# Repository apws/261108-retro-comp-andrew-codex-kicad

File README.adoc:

= Andrew's Z80: Codex KiCad experiments
:title: {docname}
:toc:

*2026-11-10:* The link:schematics/03-schematic-7805/schematic-7805.kicad_pro[separate 7805 supply schematic] and link:docs/261110-0001-DONE-schematic-7805-and-readable-wiring.adoc[wired-drawing readability cleanup] are complete. The new link:firstz80/README.adoc[FirstZ80 comparison] preserves Andrew's exact historical placement in three checked outputs: Manhattan, an explicitly labelled octilinear hybrid, and FreeRouting with a recorded native clearance correction. See link:docs/261110-0004-DONE-FirstZ80-fixed-placement-routing.adoc[the results, source differences and limitations] or link:output/firstz80/comparison.png[the comparison overview]. This is a separate two-layer series from the earlier four-layer experiments below.

*2026-11-09:* A separate link:schematics/02-wired-a3/Z80_Simple_Computer.kicad_pro[wired single-A3 schematic] is now available, with link:output/pdf/Z80_Simple_Computer-wired-A3.pdf[PDF] and link:output/schematic-wired-a3/Z80_Simple_Computer.png[PNG] previews. It preserves all 301 pin assignments, passes ERC, and retains the original schematic and completed board variants unchanged. See link:docs/261109-1528-SCHEMATIC-wired-A3.adoc[the drawing handover].

Falken's subsequent presentation refinements are retained in this human-edited version. See link:docs/261109-1549-REVIEW-human-schematic-corrections.adoc[the human-corrections review], including two unintended wiring changes repaired, six label anchors reattached and compact reminders for later sessions. The current result again matches all 301 original pin assignments with zero ERC findings.

link:docs/261109-2306-REVIEW-Mark-schematic-readability.adoc[Mark's subsequent readability review] preserves his feedback verbatim, confirms the connected but ambiguous PPI reset-pin approach, and records text/pin clearance lessons for our own drawing style. Fresh ERC and all 301 pin assignments still pass; this review does not change the schematic or resume PCB routing.

== Start here, Andrew

This repository preserves three completed routing experiments on the same 160 x 100 mm, four-layer Z80 board placement. Open the FreeRouting project first for the most economical completed routing in this comparison, then compare the saved alternatives. The original GIF and Grok/AGY project are under `reference/`.

[cols="2,1,1,3",options="header"]
|===
|Experiment |Added signal vias |Signal copper |KiCad project
|1: adapted AGY Manhattan router |212 |5,413.942 mm |link:layouts/01-reused-agy-router/Z80_Simple_Computer.kicad_pro[Open variant 1]
|2: Codex octilinear router |129 |4,959.519 mm |link:layouts/02-codex-router/Z80_Simple_Computer.kicad_pro[Open variant 2]
|4: FreeRouting, local MCP |12 |4,856.931 mm |link:layouts/04-freerouting/Z80_Simple_Computer.kicad_pro[Open variant 4]
|===

All three completed boards passed fresh native ERC/DRC/connectivity/parity checks before the initial Git snapshot. Variant 3 is the prepared native interactive experiment and remains pending. These are design experiments; hardware and signal integrity have not been qualified. FreeRouting's separate CLI controls remained incomplete and are retained as evidence.

The repository includes the required symbol, footprint and STEP library subset. Clone it with Git to preserve the relative library symlinks. The projects were checked with KiCad 10.0.8. See link:docs/261108-2026-HANDOVER-GitHub-and-next-review.adoc[publication checks, reproduction instructions and next review] for the handover.

== Working notes

The Asciidoctor.js CSS/JavaScript rendering setup is by Falken (https://mixworx.net[mixworx.net]). The local JavaScript helper also contains the filename-to-print-title adaptation described below.

Name new AsciiDoc notes under `docs/` with a `YYMMDD-HHMM` prefix, followed by a descriptive title.

New notes also use `:title: {docname}` for the HTML browser/print title. For Asciidoctor.js Live Preview, select this project's `asciidoctorjs-crx-mixworx.js` as the custom JavaScript, loaded *after* rendering, then reload the note. It retains the shared heading/key formatting and sets the tab title from the source filename, so Chromium's Save as PDF can suggest the matching `.pdf` name. See link:docs/261108-1513-DOCS-PDF-filenames.adoc[setup and verification].

*Current result:* link:docs/261108-1641-DONE-FreeRouting-MCP-and-CLI.adoc[variant 4, official local FreeRouting MCP, is fully routed and verified], with 12 vias and 4,856.931 mm of signal copper. Final ERC, DRC, unconnected and parity counts are all zero. Open link:layouts/04-freerouting/Z80_Simple_Computer.kicad_pro[the FreeRouting KiCad project] or view link:output/routing/04-freerouting/signals.png[its routing] and link:output/routing/04-freerouting/3d-top.png[3D render]. Two CLI controls remained incomplete with six connections; they are recorded separately and were not promoted as finished results.

link:docs/261108-1601-DONE-Codex-router-comparison.adoc[Variant 2, the Codex octilinear router], is preserved at 129 vias and 4,959.519 mm of signal copper, on the same placement/circuit/rules. Open link:layouts/02-codex-router/Z80_Simple_Computer.kicad_pro[its KiCad project] or link:output/routing/02-codex-router/signals.png[routing preview].

link:docs/261108-1535-DONE-routing-and-comparison.adoc[Variant 1, the adapted AGY router], remains preserved and verified: 212 vias / 5,413.942 mm. Open link:layouts/01-reused-agy-router/Z80_Simple_Computer.kicad_pro[its KiCad project] or link:output/routing/01-reused-agy-router/signals.png[routing preview]. The historical Grok/AGY board remains available for context at 229 vias / 5,036.484 mm.

The link:docs/261108-1507-RECOVERY-current-state.adoc[earlier recovery note] records the previous stopping point and conversation gap. Its schematic/placement milestone was followed by the completed routing above.

Start with link:docs/261108-1419-PLAN.adoc[the experiment plan] and link:docs/261108-1422-PLAN-project-layouts.adoc[the agreed project organization].

`design/Z80_Simple_Computer.kicad_pro` is the authoritative circuit project. It now contains the Codex A3 schematic base, generated from an explicit pin specification and checked against the source GIF and inherited netlist. See link:docs/261108-1438-SCHEMATIC-base.adoc[the schematic handover] and `design/provenance.json`.

Open link:output/schematic/Z80_Simple_Computer.svg[the schematic preview] or link:output/schematic/Z80_Simple_Computer.png[the PNG rendering]. The native netlist and CSV BOM are in `output/schematic/`; ERC and connectivity reports are in `reports/schematic/`.

`layouts/` contains four ordinary KiCad project folders for the AGY-router reuse, Codex-router, interactive-KiCad, and FreeRouting experiments. Each has its own project settings and a synchronized schematic. Variants 1, 2 and 4 now contain completed routed Eurocards. link:docs/261108-1613-PENDING-native-interactive.adoc[Variant 3 is prepared and remains unrouted] for a later native GUI/control session; its worksheet and initial checks are saved. The completed historical board remains under `reference/grok-agy/`.

The link:docs/261108-1500-PLACEMENT-checkpoint.adoc[placement handover] includes a link:output/placement/3d-top.png[3D preview], verification and reproduction commands. `checkpoints/01-codex-placed-unrouted/` preserves the common routing input with file hashes. That untouched checkpoint has 138 expected unconnected items and no signal tracks; the working layout has since been fully routed. Each of the seven checked routing stages is preserved under `reports/routing/01-reused-agy-router/`.

[source,shell]
----
python3 tools/sync_layouts.py --check
python3 tools/sync_layouts.py --sync
python3 tools/sync_layouts.py --sync --layout 01-reused-agy-router
----

Edit circuit connectivity in `design/`. Layout schematic snapshots are managed copies; the synchronizer refuses local edits. It preserves each existing layout project file and PCB. Set an experiment's `frozen` manifest flag to retain a historical schematic input. See the organization plan for library-link portability, board update requirements, and fair comparisons.

The current capture uses `design/circuit.json` for pin assignments and `tools/build_schematic.py` for drawing geometry. Regeneration with `python3 tools/build_schematic.py --write` preserves deterministic component UUIDs and refuses unreviewed edits to the generated schematic. If adopting manual KiCad schematic editing, stop regeneration and maintain the `.kicad_sch` directly; synchronization still copies that authoritative file normally.

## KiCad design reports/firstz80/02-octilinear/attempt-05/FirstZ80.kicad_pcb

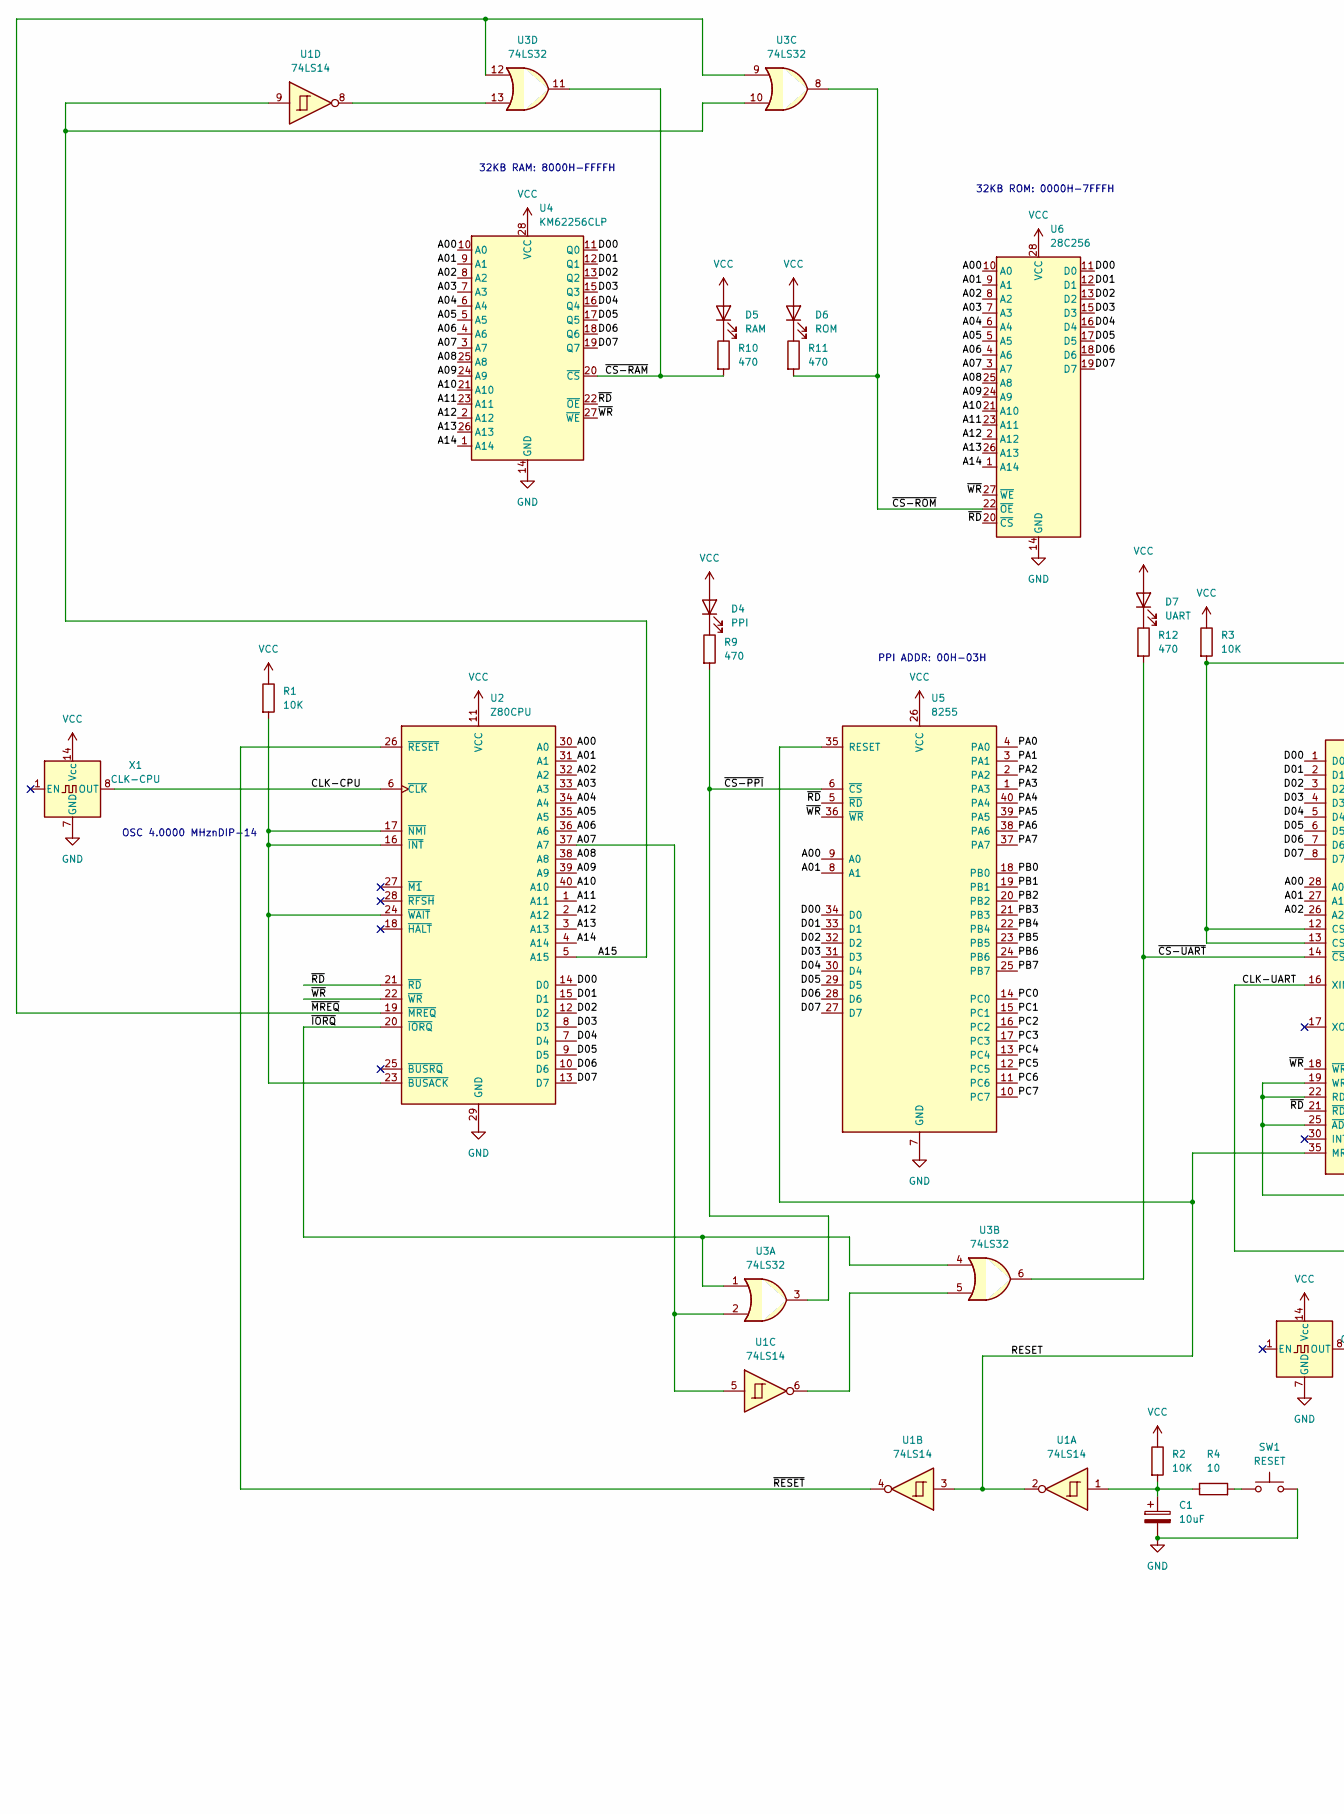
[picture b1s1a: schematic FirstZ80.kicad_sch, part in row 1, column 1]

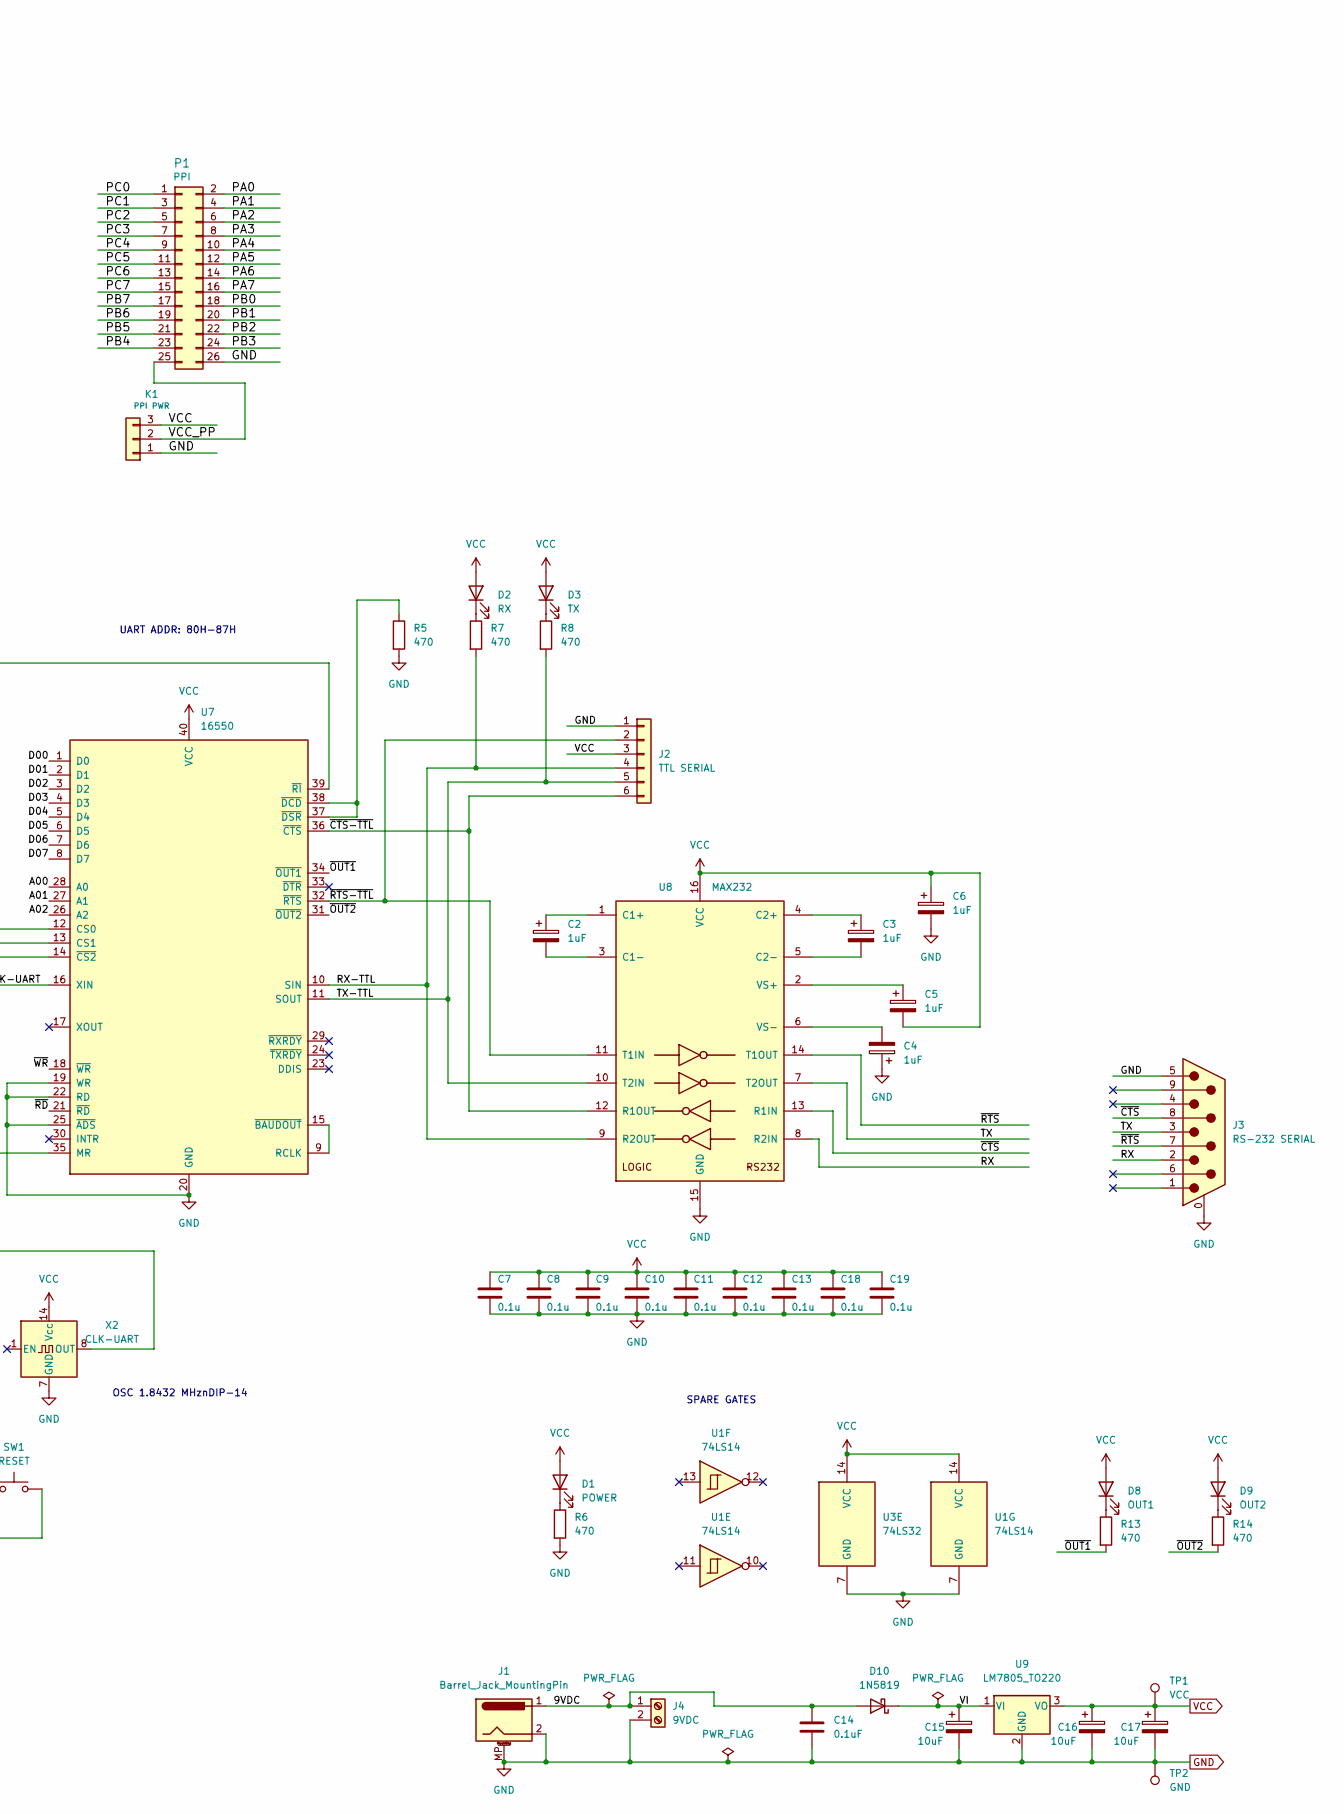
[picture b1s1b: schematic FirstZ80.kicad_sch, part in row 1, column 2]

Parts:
C1, C15, C16, C17: 10uF; Capacitor_THT__CP_Radial_D5.0mm_P2.50mm
C2, C3, C4, C5, C6: 1uF; Capacitor_THT__CP_Radial_D5.0mm_P2.50mm
C7, C8, C9, C10, C11, C12, C13, C18, C19: 0.1u; Capacitor_THT__C_Disc_D5.0mm_W2.5mm_P5.00mm
C14: 0.1uF; Capacitor_THT__C_Disc_D5.0mm_W2.5mm_P5.00mm
D1: POWER; LED_THT__LED_D3.0mm
D2: RX; LED_THT__LED_D3.0mm
D3: TX; LED_THT__LED_D3.0mm
D4: PPI; LED_THT__LED_D3.0mm
D5: RAM; LED_THT__LED_D3.0mm
D6: ROM; LED_THT__LED_D3.0mm
D7: UART; LED_THT__LED_D3.0mm
D8: OUT1; LED_THT__LED_D3.0mm
D9: OUT2; LED_THT__LED_D3.0mm
D10: 1N5819; Diode_THT__D_DO-41_SOD81_P10.16mm_Horizontal
J1: Barrel_Jack_MountingPin; Connector_BarrelJack__BarrelJack_Horizontal
J2: TTL SERIAL; Connector_PinHeader_2.54mm__PinHeader_1x06_P2.54mm_Horizont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
J3: RS-232 SERIAL; Connector_Dsub__DSUB-9_Male_Horizontal_P2.77x2.84mm_EdgePin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
J4: 9VDC; TerminalBlock_Phoenix__TerminalBlock_Phoenix_MKDS-1,5-2-5.0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
K1: PPI PWR; Connector_PinHeader_2.54mm__PinHeader_1x03_P2.54mm_Vertical
P1: PPI; Connector_IDC__IDC-Header_2x13_P2.54mm_Horizontal
R1, R2, R3: 10K; Resistor_THT__R_Axial_DIN0207_L6.3mm_D2.5mm_P7.62mm_Horizon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
R4: 10; Resistor_THT__R_Axial_DIN0207_L6.3mm_D2.5mm_P7.62mm_Horizon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
R5, R6, R7, R8, R9, R10, R11, R12, R13, R14: 470; Resistor_THT__R_Axial_DIN0207_L6.3mm_D2.5mm_P7.62mm_Horizon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
SW1: RESET; Button_Switch_THT__SW_PUSH_6mm
TP1: VCC; Connector_PinHeader_2.54mm__PinHeader_1x01_P2.54mm_Vertical
TP2: GND; Connector_PinHeader_2.54mm__PinHeader_1x01_P2.54mm_Vertical
U1: 74LS14; Package_DIP__DIP-14_W7.62mm_Socket_LongPads
U2: Z80CPU; Package_DIP__DIP-40_W15.24mm_Socket_LongPads
U3: 74LS32; Package_DIP__DIP-14_W7.62mm_Socket_LongPads
U4: KM62256CLP; Package_DIP__DIP-28_W15.24mm_Socket_LongPads
U5: 8255; Package_DIP__DIP-40_W15.24mm_Socket_LongPads
U6: 28C256; Package_DIP__DIP-28_W15.24mm_Socket_LongPads
U7: 16550; Package_DIP__DIP-40_W15.24mm_Socket_LongPads
U8: MAX232; Package_DIP__DIP-16_W7.62mm_Socket_LongPads
U9: LM7805_TO220; Package_TO_SOT_THT__TO-220-3_Horizontal_TabDown
X1: CLK-CPU; Oscillator__Oscillator_DIP-14
X2: CLK-UART; Oscillator__Oscillator_DIP-14

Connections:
/9VDC: C14.1, D10.2 (A), J1.1, J4.1
/A00: U2.30 (A0), U4.10 (A0), U5.9 (A0), U6.10 (A0), U7.28 (A0)
/A01: U2.31 (A1), U4.9 (A1), U5.8 (A1), U6.9 (A1), U7.27 (A1)
/A02: U2.32 (A2), U4.8 (A2), U6.8 (A2), U7.26 (A2)
/A03: U2.33 (A3), U4.7 (A3), U6.7 (A3)
/A04: U2.34 (A4), U4.6 (A4), U6.6 (A4)
/A05: U2.35 (A5), U4.5 (A5), U6.5 (A5)
/A06: U2.36 (A6), U4.4 (A6), U6.4 (A6)
/A07: U1.5, U2.37 (A7), U3.2, U4.3 (A7), U6.3 (A7)
/A08: U2.38 (A8), U4.25 (A8), U6.25 (A8)
/A09: U2.39 (A9), U4.24 (A9), U6.24 (A9)
/A10: U2.40 (A10), U4.21 (A10), U6.21 (A10)
/A11: U2.1 (A11), U4.23 (A11), U6.23 (A11)
/A12: U2.2 (A12), U4.2 (A12), U6.2 (A12)
/A13: U2.3 (A13), U4.26 (A13), U6.26 (A13)
/A14: U2.4 (A14), U4.1 (A14), U6.1 (A14)
/A15: U1.9, U2.5 (A15), U3.10
/CLK-CPU: U2.6 (~CLK), X1.8 (OUT)
/CLK-UART: U7.16 (XIN), X2.8 (OUT)
/D00: U2.14 (D0), U4.11 (Q0), U5.34 (D0), U6.11 (D0), U7.1 (D0)
/D01: U2.15 (D1), U4.12 (Q1), U5.33 (D1), U6.12 (D1), U7.2 (D1)
/D02: U2.12 (D2), U4.13 (Q2), U5.32 (D2), U6.13 (D2), U7.3 (D2)
/D03: U2.8 (D3), U4.15 (Q3), U5.31 (D3), U6.15 (D3), U7.4 (D3)
/D04: U2.7 (D4), U4.16 (Q4), U5.30 (D4), U6.16 (D4), U7.5 (D4)
/D05: U2.9 (D5), U4.17 (Q5), U5.29 (D5), U6.17 (D5), U7.6 (D5)
/D06: U2.10 (D6), U4.18 (Q6), U5.28 (D6), U6.18 (D6), U7.7 (D6)
/D07: U2.13 (D7), U4.19 (Q7), U5.27 (D7), U6.19 (D7), U7.8 (D7)
/PA0: P1.2, U5.4 (PA0)
/PA1: P1.4, U5.3 (PA1)
/PA2: P1.6, U5.2 (PA2)
/PA3: P1.8, U5.1 (PA3)
/PA4: P1.10, U5.40 (PA4)
/PA5: P1.12, U5.39 (PA5)
/PA6: P1.14, U5.38 (PA6)
/PA7: P1.16, U5.37 (PA7)
/PB0: P1.18, U5.18 (PB0)
/PB1: P1.20, U5.19 (PB1)
/PB2: P1.22, U5.20 (PB2)
/PB3: P1.24, U5.21 (PB3)
/PB4: P1.23, U5.22 (PB4)
/PB5: P1.21, U5.23 (PB5)
/PB6: P1.19, U5.24 (PB6)
/PB7: P1.17, U5.25 (PB7)
/PC0: P1.1, U5.14 (PC0)
/PC1: P1.3, U5.15 (PC1)
/PC2: P1.5, U5.16 (PC2)
/PC3: P1.7, U5.17 (PC3)
/PC4: P1.9, U5.13 (PC4)
/PC5: P1.11, U5.12 (PC5)
/PC6: P1.13, U5.11 (PC6)
/PC7: P1.15, U5.10 (PC7)
/RESET: U1.2, U1.3, U5.35 (RESET), U7.35 (MR)
/RX: J3.2, U8.8 (R2IN)
/RX-TTL: J2.4, R7.2, U7.10 (SIN), U8.9 (R2OUT)
/TX: J3.3, U8.7 (T2OUT)
/TX-TTL: J2.5, R8.2, U7.11 (SOUT), U8.10 (T2IN)
/VCC_PP: K1.2, P1.25
/VI: C15.1, D10.1 (K), U9.1 (VI)
/~CS-PPI: R9.2, U3.3, U5.6 (~CS)
/~CS-RAM: R10.2, U3.11, U4.20 (~CS)
/~CS-ROM: R11.2, U3.8, U6.22 (~OE)
/~CS-UART: R12.2, U3.6, U7.14 (~CS2)
/~CTS-TTL: J2.6, U7.36 (~CTS), U8.12 (R1OUT)
/~CTS: J3.8, U8.13 (R1IN)
/~IORQ: U2.20 (~IORQ), U3.1, U3.4
/~MREQ: U2.19 (~MREQ), U3.9, U3.12
/~OUT1: R13.2, U7.34 (~OUT1)
/~OUT2: R14.2, U7.31 (~OUT2)
/~RD: U2.21 (~RD), U4.22 (~OE), U5.5 (~RD), U6.20 (~CS), U7.21 (~RD)
/~RESET: U1.4, U2.26 (~RESET)
/~RTS-TTL: J2.2, U7.32 (~RTS), U8.11 (T1IN)
/~RTS: J3.7, U8.14 (T1OUT)
/~WR: U2.22 (~WR), U4.27 (~WE), U5.36 (~WR), U6.27 (~WE), U7.18 (~WR)
GND: C1.2, C4.1, C6.2, C7.2, C8.2, C9.2, C10.2, C11.2, C12.2, C13.2, C14.2, C15.2, C16.2, C17.2, C18.2, C19.2, J1.2, J1.MP (MountPin), J2.1, J3.0 (PAD), J3.5, J4.2, K1.1, P1.26, R5.2, R6.2, SW1.2, TP2.1, U1.7 (GND), U2.29 (GND), U3.7 (GND), U4.14 (GND), U5.7 (GND), U6.14 (GND), U7.19 (WR), U7.20 (GND), U7.22 (RD), U7.25 (~ADS), U8.15 (GND), U9.2 (GND), X1.7 (GND), X2.7 (GND)
unnamed: C1.1, R2.2, R4.1, U1.1
unnamed: D1.1 (K), R6.1
unnamed: D2.1 (K), R7.1
unnamed: D3.1 (K), R8.1
unnamed: D4.1 (K), R9.1
unnamed: D5.1 (K), R10.1
unnamed: D6.1 (K), R11.1
unnamed: D7.1 (K), R12.1
unnamed: D8.1 (K), R13.1
unnamed: D9.1 (K), R14.1
unnamed: R4.2, SW1.1
unnamed: U1.6, U3.5
unnamed: U1.8, U3.13
unnamed: R1.2, U2.16 (~INT), U2.17 (~NMI), U2.23 (~BUSACK), U2.24 (~WAIT)
unnamed: R3.2, U7.12 (CS0), U7.13 (CS1), U7.39 (~RI)
unnamed: U7.9 (RCLK), U7.15 (~BAUDOUT)
unnamed: R5.1, U7.37 (~DSR), U7.38 (~DCD)
unnamed: C2.1, U8.1 (C1+)
unnamed: C2.2, U8.3 (C1-)
unnamed: C3.1, U8.4 (C2+)
unnamed: C3.2, U8.5 (C2-)
unnamed: C5.1, U8.2 (VS+)
unnamed: C4.2, U8.6 (VS-)
VCC: C5.2, C6.1, C7.1, C8.1, C9.1, C10.1, C11.1, C12.1, C13.1, C16.1, C17.1, C18.1, C19.1, D1.2 (A), D2.2 (A), D3.2 (A), D4.2 (A), D5.2 (A), D6.2 (A), D7.2 (A), D8.2 (A), D9.2 (A), J2.3, K1.3, R1.1, R2.1, R3.1, TP1.1, U1.14 (VCC), U2.11 (VCC), U3.14 (VCC), U4.28 (VCC), U5.26 (VCC), U6.28 (VCC), U7.40 (VCC), U8.16 (VCC), U9.3 (VO), X1.14 (Vcc), X2.14 (Vcc)

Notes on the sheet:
UART ADDR: 80H-87H
SPARE GATES
PPI ADDR: 00H-03H
OSC 1.8432 MHznDIP-14
32KB ROM: 0000H-7FFFH
32KB RAM: 8000H-FFFFH
OSC 4.0000 MHznDIP-14

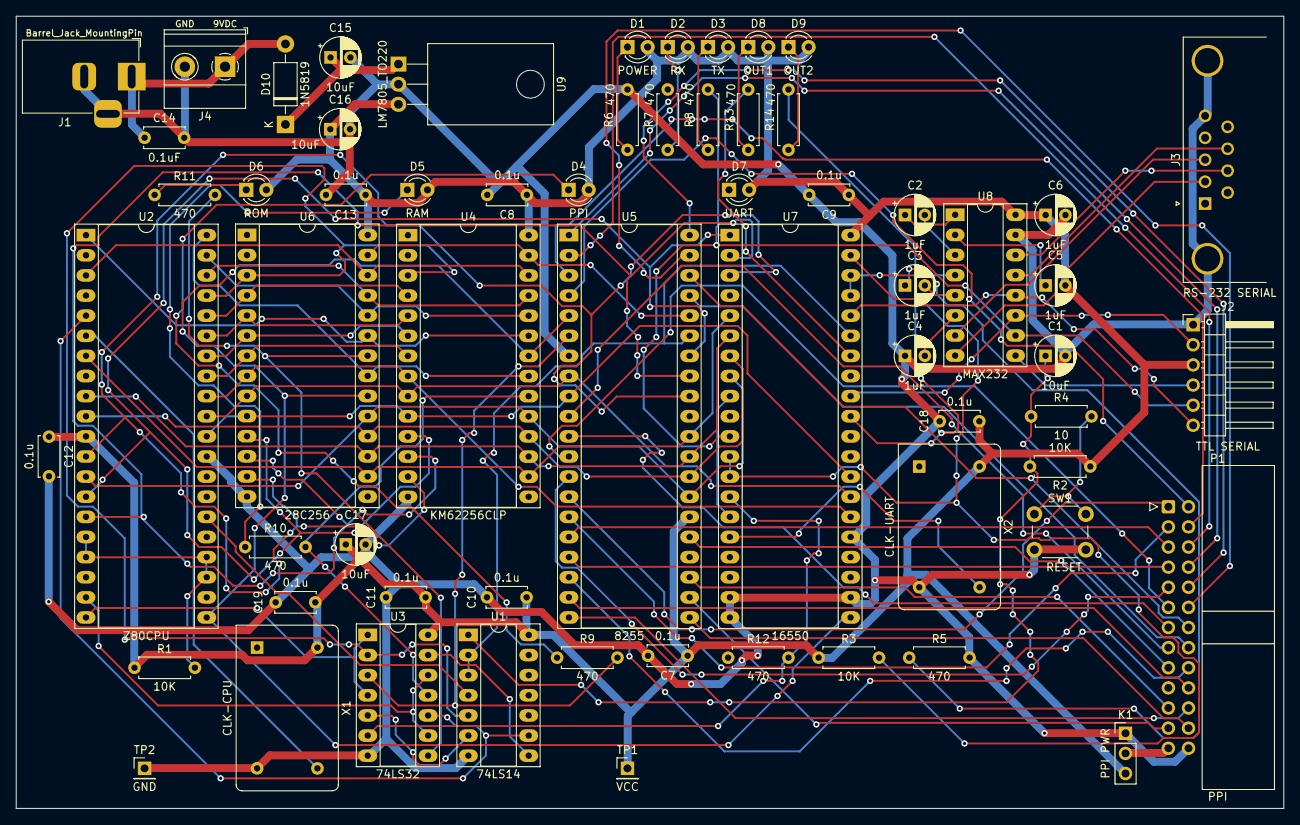
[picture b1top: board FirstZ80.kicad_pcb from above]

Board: 2 copper layers, 160.0 x 100.0 mm, 63 parts (0 on the bottom side), 98 nets.

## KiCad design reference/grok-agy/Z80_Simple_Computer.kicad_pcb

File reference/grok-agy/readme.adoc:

= Z80 simple computer
:toc:
:toclevels: 2

The schematic is the rebuilt sheet. It opens, it uses stock KiCad 10.0.7 symbols, and the parts now sit inside the paper. The notes under `docs/` say how that was done.

The PCB file in this directory is not the posted board. That file would not open, and it is kept unchanged in `as-posted/`. The project board is a new KiCad 10 board. What is on it now is the Eurocard outline, the parts placed on the top, four layers, the inner ground and +5V planes, and all signal tracks 100% routed. The DE9 plug hangs off the left edge. The screw-terminal holes hang off the right edge. The STEP models are in `libs/kicad-packages3D-10.0.7/`, and the board names them with `${KIPRJMOD}`, the project directory.

The choices for this trial are in the plan. The sheet is A3, because the DIP-40 symbols do not fit A4. The board is a 160 by 100 mm Eurocard, four layers, a screw terminal for +5V, four M3 holes, and tracks written into the board file. FreeRouting was not used.

Tooling timeline:

* *Schematic rebuild, placement, and 3D modeling*: Conducted collaboratively using `grok-cli` (Grok 3 in terminal).
* *Automated PCB routing*: Handed over to Google Antigravity (`agy`), using an in-tree Python Manhattan router (`tools/route_netgroup.py`) via KiCad's `pcbnew` Python API.

Routing status:
All signal net groups have been routed and verified via KiCad DRC with 0 clearance violations, 0 shorts, and 0 unconnected items (100% routed):

. Group 1 (clocks and reset) is routed cleanly with 0 DRC errors.
. Group 2 (MAX232 charge pump, DE9 serial, and UART TTL lines) is routed cleanly with 0 DRC errors.
. Group 3 (Data bus D0-D7 across CPU, RAM, ROM, PIO, and UART) is routed cleanly with 0 DRC errors.
. Group 4 (Lower address A0-A2 and chip-select decodes) is routed cleanly with 0 DRC errors.
. Group 5 (Control strobes /RD, /WR, /MREQ, /IORQ and decode inputs A7, A15) is routed cleanly with 0 DRC errors.
. Group 6 (Upper address bus A3-A6, A8-A14 across CPU, RAM, and ROM) is routed cleanly with 0 DRC errors.
. Group 7 (UART BAUDOUT loop and PIO Port A, Port B, Port C headers J2, J3, J4) is routed cleanly with 0 DRC errors. Board unconnected items: 0.

`tools/build_schematic.py` rewrites the schematic. If you move a part in KiCad and then run that script, the script wins. Either edit in KiCad and stop using the script, or change the script. Do not do both.

Read these first:

* link:docs/261103-what-went-wrong-and-how-to-do-it.adoc[Why the posted files are not a computer]
* link:docs/261103-a-guide-for-andrew.adoc[Doing the sheet one step at a time]
* link:docs/261104-00%20Chat%20transcript%20--%20fitting%20the%20symbols%20inside%20the%20frame.adoc[Fitting the symbols inside the frame]
* link:docs/261104-01%20Plan%20--%20placing%20and%20routing%20the%20board.adoc[Plan for placing and routing the board]
* link:docs/261104-02%20Chat%20transcript%20--%20the%20board%20plan%20and%20the%20public%20repo.adoc[The board plan, and the public repository]
* link:docs/261105-22%20Placing%20the%20Eurocard%20and%20the%20first%20tracks.adoc[Placing the Eurocard, and the first tracks]
* link:docs/261105-22%20JLCPCB%20rules%20for%20this%20board.adoc[JLCPCB rules for this board]
* link:docs/261105-23%20Placement%20only,%20connectors%20facing%20out.adoc[Placement only, connectors facing out]
* link:docs/261105-23%203D%20models%20for%20the%20footprints.adoc[3D models for the footprints]
* link:docs/261106-12%20Screw%20terminal%20holes%20facing%20out.adoc[Screw terminal holes facing out]
* link:docs/261106-12%20Capacitors%20beside%20the%20power%20pins.adoc[Capacitors beside the power pins]
* link:docs/261106-12%20MAX232%20beside%20the%20DE9.adoc[MAX232 beside the DE9]
* link:docs/261106-12%20Andrew's%20design%20brief.adoc[Andrew's design brief]
* link:docs/261106-12%20Where%20Andrew's%20brief%20meets%20this%20board.adoc[Where Andrew's brief meets this board]
* link:docs/261106-18%20Handover%20to%20Google%20Antigravity%20and%20automated%20routing%20approach.adoc[Handover to Google Antigravity and automated routing approach]
* link:docs/261106-19%20First%20routed%20tracks%20--%20clocks%20and%20reset.adoc[First routed tracks -- clocks and reset]
* link:docs/261106-19%20Second%20routed%20tracks%20--%20MAX232%20and%20DE9.adoc[Second routed tracks -- MAX232 and DE9]
* link:docs/261106-20%20Third%20routed%20tracks%20--%20data%20bus%20D0-D7.adoc[Third routed tracks -- data bus D0-D7]
* link:docs/261106-20%20Fourth%20routed%20tracks%20--%20lower%20address%20and%20chip%20selects.adoc[Fourth routed tracks -- lower address and chip selects]
* link:docs/261106-20%20Fifth%20routed%20tracks%20--%20control%20strobes%20and%20decode%20inputs.adoc[Fifth routed tracks -- control strobes and decode inputs]
* link:docs/261106-21%20Sixth%20routed%20tracks%20--%20upper%20address%20bus%20A3-A14.adoc[Sixth routed tracks -- upper address bus A3-A14]
* link:docs/261106-21b%20Seventh%20routed%20tracks%20--%20peripheral%20IO%20and%20baudout.adoc[Seventh routed tracks -- peripheral IO and baudout]

== Previewing these notes

For a formatted view in Chrome or Chromium, install
https://chromewebstore.google.com/detail/asciidoctorjs-live-previe/iaalpfgpbocpdfblpnhhgllgbdbchmia[Asciidoctor.js Live Preview].
Enable *Allow access to file URLs* on the extension's details page, then open a local `.adoc` file.
The https://docs.asciidoctor.org/browser-extension/install/[installation notes] also mention Edge. Edge has not been tried here.

The two files in this directory are the Mixworx preview style used by the other local projects. Select them in the extension options:

* link:asciidoctorjs-crx-mixworx.css[asciidoctorjs-crx-mixworx.css]: stylesheet for type, headings, tables, code, and print.
* link:asciidoctorjs-crx-mixworx.js[asciidoctorjs-crx-mixworx.js]: run this *after the document has been rendered*. It marks modifier keys, splits a heading at the first prose colon, and puts anchor positions back after rendering.

If the repository moves, or either file changes, select them again in the extension options.
GitHub itself still shows the normal colon in a heading. The line break is only in this local preview.

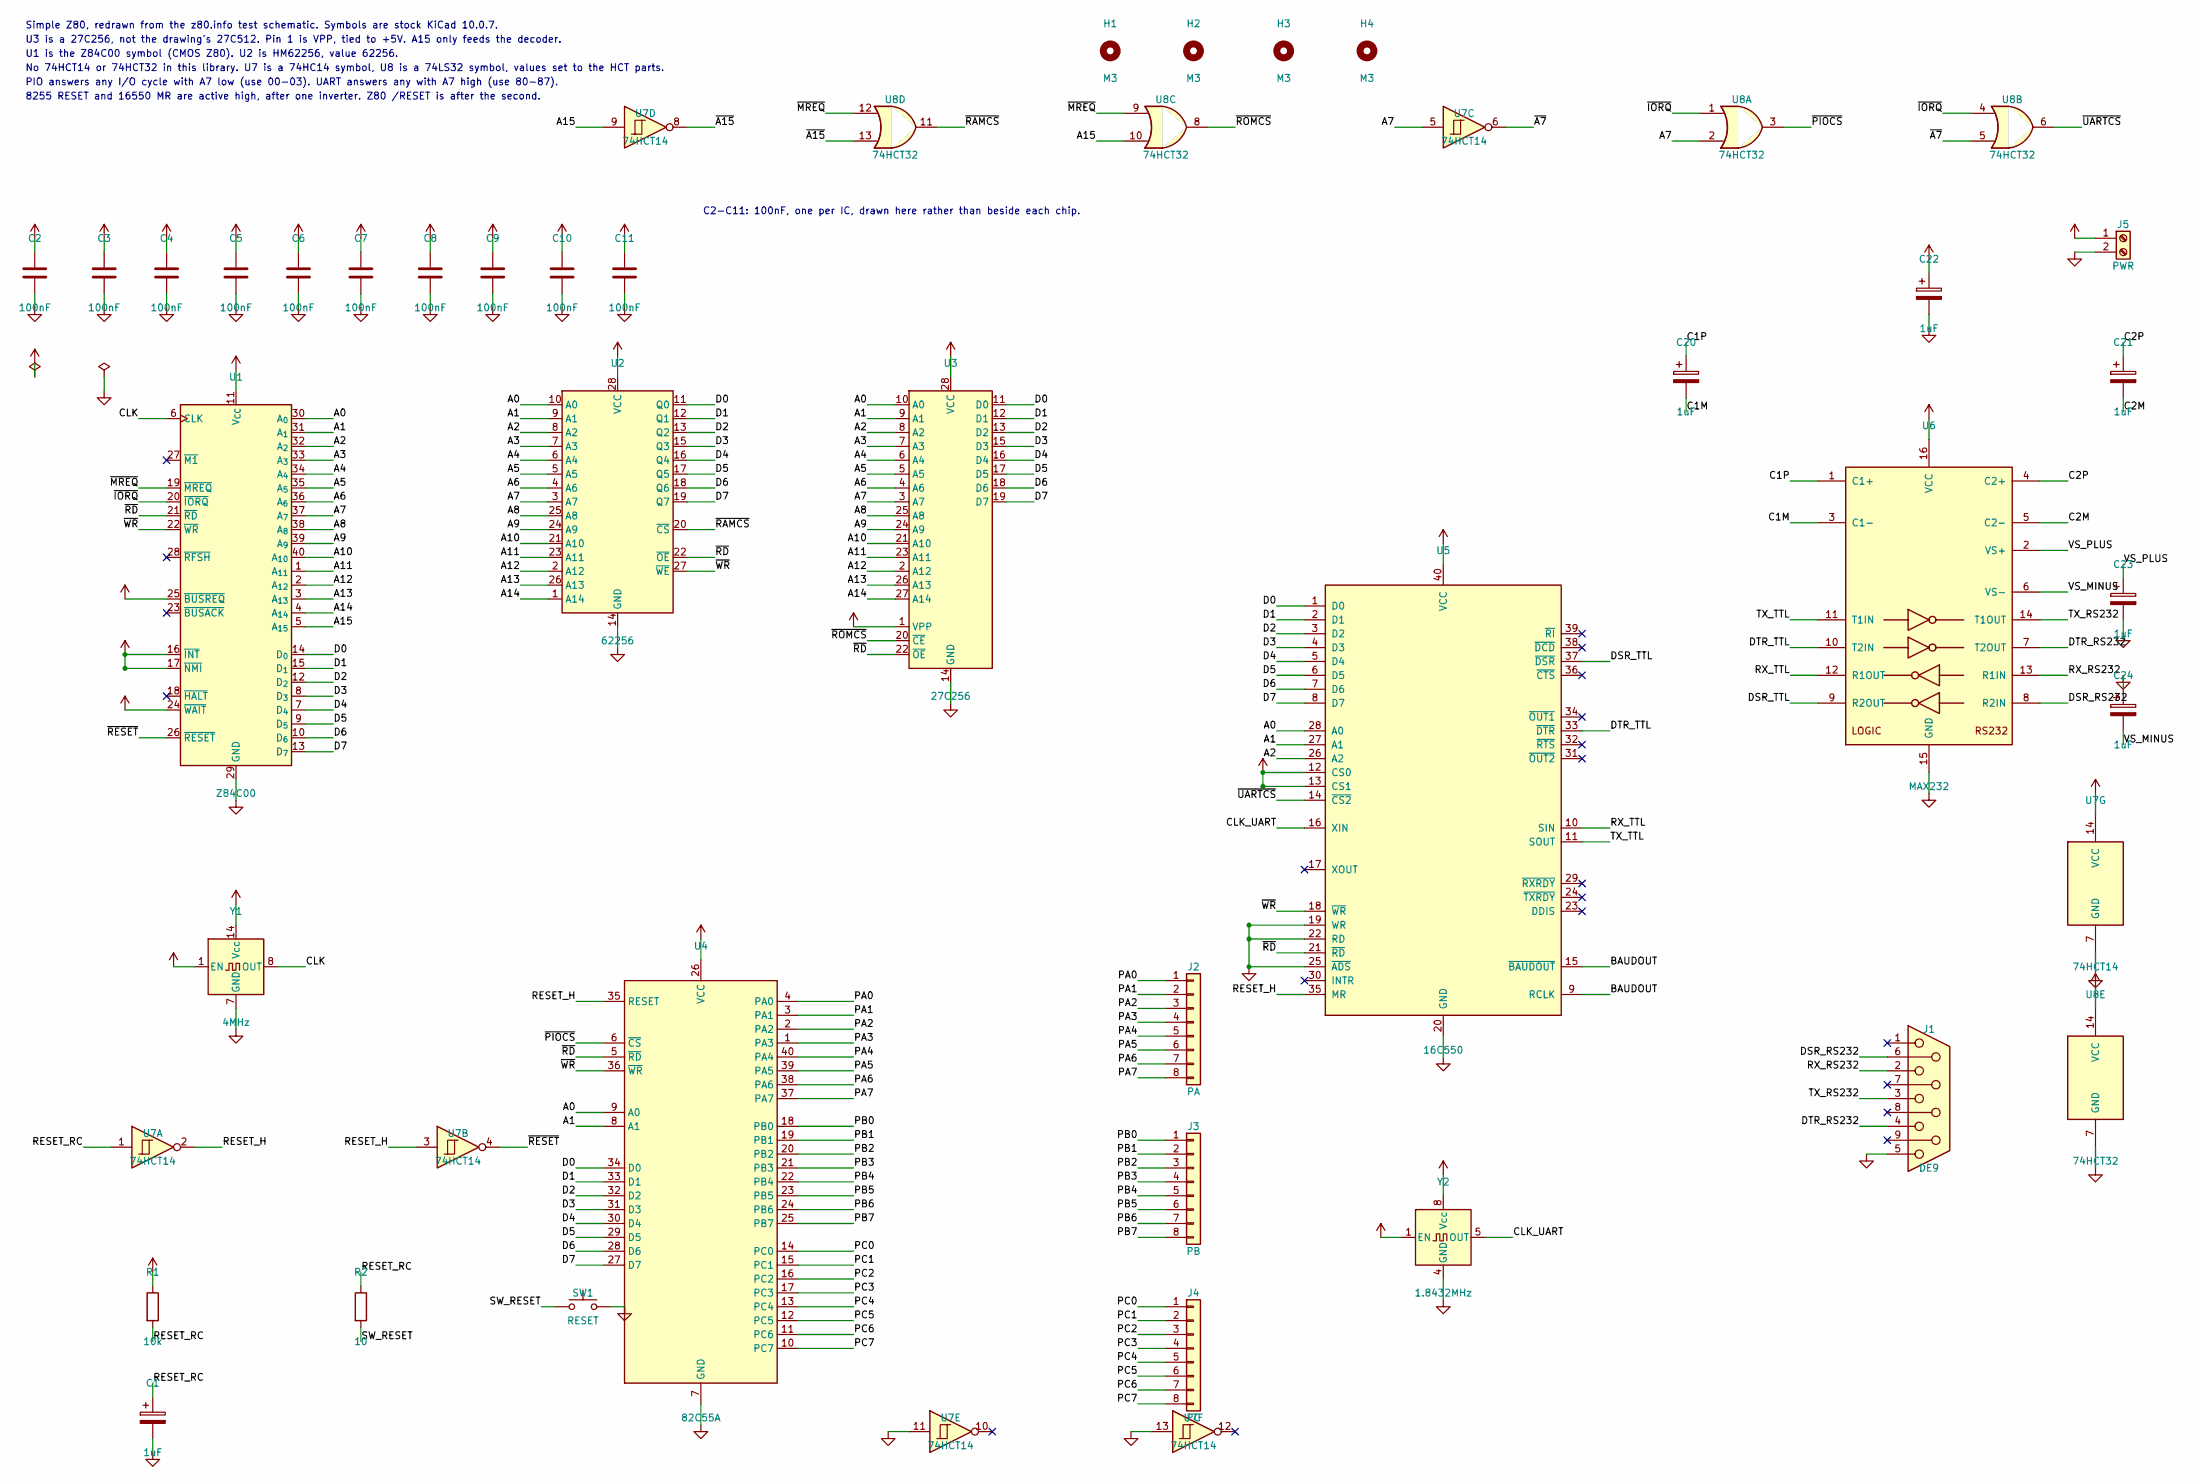
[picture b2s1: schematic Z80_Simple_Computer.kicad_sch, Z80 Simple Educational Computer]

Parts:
C1, C20, C21, C22, C23, C24: 1uF; CP_Radial_D5.0mm_P2.50mm
C2, C3, C4, C5, C6, C7, C8, C9, C10, C11: 100nF; C_Disc_D5.0mm_W2.5mm_P5.00mm
H1, H2, H3, H4: M3; MountingHole_3.2mm_M3
J1: DE9; DSUB-9_Socket_Horizontal_P2.77x2.84mm_EdgePinOffset4.94mm_H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
J2: PA; PinHeader_1x08_P2.54mm_Vertical
J3: PB; PinHeader_1x08_P2.54mm_Vertical
J4: PC; PinHeader_1x08_P2.54mm_Vertical
J5: PWR; TerminalBlock_Phoenix_MKDS-1,5-2-5.08_1x02_P5.08mm_Horizont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
R1: 10k; R_Axial_DIN0207_L6.3mm_D2.5mm_P10.16mm_Horizontal
R2: 10; R_Axial_DIN0207_L6.3mm_D2.5mm_P10.16mm_Horizontal
SW1: RESET; SW_PUSH_6mm
U1: Z84C00; DIP-40_W15.24mm
U2: 62256; DIP-28_W15.24mm
U3: 27C256; DIP-28_W15.24mm
U4: 82C55A; DIP-40_W15.24mm
U5: 16C550; DIP-40_W15.24mm
U6: MAX232; DIP-16_W7.62mm
U7: 74HCT14; DIP-14_W7.62mm
U8: 74HCT32; DIP-14_W7.62mm
Y1: 4MHz; Oscillator_DIP-14
Y2: 1.8432MHz; Oscillator_DIP-8

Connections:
+5V: C2.1, C3.1, C4.1, C5.1, C6.1, C7.1, C8.1, C9.1, C10.1, C11.1, C22.1, J5.1, R1.1, U1.11 (V_{CC}), U1.16 (~INT), U1.17 (~NMI), U1.24 (~WAIT), U1.25 (~BUSREQ), U2.28 (VCC), U3.1 (VPP), U3.28 (VCC), U4.26 (VCC), U5.12 (CS0), U5.13 (CS1), U5.40 (VCC), U6.16 (VCC), U7.14 (VCC), U8.14 (VCC), Y1.1 (EN), Y1.14 (Vcc), Y2.1 (EN), Y2.8 (Vcc)
/A0: U1.30 (A_{0}), U2.10 (A0), U3.10 (A0), U4.9 (A0), U5.28 (A0)
/A1: U1.31 (A_{1}), U2.9 (A1), U3.9 (A1), U4.8 (A1), U5.27 (A1)
/A2: U1.32 (A_{2}), U2.8 (A2), U3.8 (A2), U5.26 (A2)
/A3: U1.33 (A_{3}), U2.7 (A3), U3.7 (A3)
/A4: U1.34 (A_{4}), U2.6 (A4), U3.6 (A4)
/A5: U1.35 (A_{5}), U2.5 (A5), U3.5 (A5)
/A6: U1.36 (A_{6}), U2.4 (A6), U3.4 (A6)
/A7: U1.37 (A_{7}), U2.3 (A7), U3.3 (A7), U7.5, U8.2
/A8: U1.38 (A_{8}), U2.25 (A8), U3.25 (A8)
/A9: U1.39 (A_{9}), U2.24 (A9), U3.24 (A9)
/A10: U1.40 (A_{10}), U2.21 (A10), U3.21 (A10)
/A11: U1.1 (A_{11}), U2.23 (A11), U3.23 (A11)
/A12: U1.2 (A_{12}), U2.2 (A12), U3.2 (A12)
/A13: U1.3 (A_{13}), U2.26 (A13), U3.26 (A13)
/A14: U1.4 (A_{14}), U2.1 (A14), U3.27 (A14)
/A15: U1.5 (A_{15}), U7.9, U8.10
/BAUDOUT: U5.9 (RCLK), U5.15 (~BAUDOUT)
/C1M: C20.2, U6.3 (C1-)
/C1P: C20.1, U6.1 (C1+)
/C2M: C21.2, U6.5 (C2-)
/C2P: C21.1, U6.4 (C2+)
/CLK: U1.6 (CLK), Y1.8 (OUT)
/CLK_UART: U5.16 (XIN), Y2.5 (OUT)
/D0: U1.14 (D_{0}), U2.11 (Q0), U3.11 (D0), U4.34 (D0), U5.1 (D0)
/D1: U1.15 (D_{1}), U2.12 (Q1), U3.12 (D1), U4.33 (D1), U5.2 (D1)
/D2: U1.12 (D_{2}), U2.13 (Q2), U3.13 (D2), U4.32 (D2), U5.3 (D2)
/D3: U1.8 (D_{3}), U2.15 (Q3), U3.15 (D3), U4.31 (D3), U5.4 (D3)
/D4: U1.7 (D_{4}), U2.16 (Q4), U3.16 (D4), U4.30 (D4), U5.5 (D4)
/D5: U1.9 (D_{5}), U2.17 (Q5), U3.17 (D5), U4.29 (D5), U5.6 (D5)
/D6: U1.10 (D_{6}), U2.18 (Q6), U3.18 (D6), U4.28 (D6), U5.7 (D6)
/D7: U1.13 (D_{7}), U2.19 (Q7), U3.19 (D7), U4.27 (D7), U5.8 (D7)
/DSR_RS232: J1.6, U6.8 (R2IN)
/DSR_TTL: U5.37 (~DSR), U6.9 (R2OUT)
/DTR_RS232: J1.4, U6.7 (T2OUT)
/DTR_TTL: U5.33 (~DTR), U6.10 (T2IN)
/PA0: J2.1, U4.4 (PA0)
/PA1: J2.2, U4.3 (PA1)
/PA2: J2.3, U4.2 (PA2)
/PA3: J2.4, U4.1 (PA3)
/PA4: J2.5, U4.40 (PA4)
/PA5: J2.6, U4.39 (PA5)
/PA6: J2.7, U4.38 (PA6)
/PA7: J2.8, U4.37 (PA7)
/PB0: J3.1, U4.18 (PB0)
/PB1: J3.2, U4.19 (PB1)
/PB2: J3.3, U4.20 (PB2)
/PB3: J3.4, U4.21 (PB3)
/PB4: J3.5, U4.22 (PB4)
/PB5: J3.6, U4.23 (PB5)
/PB6: J3.7, U4.24 (PB6)
/PB7: J3.8, U4.25 (PB7)
/PC0: J4.1, U4.14 (PC0)
/PC1: J4.2, U4.15 (PC1)
/PC2: J4.3, U4.16 (PC2)
/PC3: J4.4, U4.17 (PC3)
/PC4: J4.5, U4.13 (PC4)
/PC5: J4.6, U4.12 (PC5)
/PC6: J4.7, U4.11 (PC6)
/PC7: J4.8, U4.10 (PC7)
/RESET_H: U4.35 (RESET), U5.35 (MR), U7.2, U7.3
/RESET_RC: C1.1, R1.2, R2.1, U7.1
/RX_RS232: J1.2, U6.13 (R1IN)
/RX_TTL: U5.10 (SIN), U6.12 (R1OUT)
/SW_RESET: R2.2, SW1.1
/TX_RS232: J1.3, U6.14 (T1OUT)
/TX_TTL: U5.11 (SOUT), U6.11 (T1IN)
/VS_MINUS: C24.2, U6.6 (VS-)
/VS_PLUS: C23.1, U6.2 (VS+)
/~A7: U7.6, U8.5
/~A15: U7.8, U8.13
/~IORQ: U1.20 (~IORQ), U8.1, U8.4
/~MREQ: U1.19 (~MREQ), U8.9, U8.12
/~PIOCS: U4.6 (~CS), U8.3
/~RAMCS: U2.20 (~CS), U8.11
/~RD: U1.21 (~RD), U2.22 (~OE), U3.22 (~OE), U4.5 (~RD), U5.21 (~RD)
/~RESET: U1.26 (~RESET), U7.4
/~ROMCS: U3.20 (~CE), U8.8
/~UARTCS: U5.14 (~CS2), U8.6
/~WR: U1.22 (~WR), U2.27 (~WE), U4.36 (~WR), U5.18 (~WR)
GND: C1.2, C2.2, C3.2, C4.2, C5.2, C6.2, C7.2, C8.2, C9.2, C10.2, C11.2, C22.2, C23.2, C24.1, J1.5, J5.2, SW1.2, U1.29 (GND), U2.14 (GND), U3.14 (GND), U4.7 (GND), U5.19 (WR), U5.20 (GND), U5.22 (RD), U5.25 (~ADS), U6.15 (GND), U7.7 (GND), U7.11, U7.13, U8.7 (GND), Y1.7 (GND), Y2.4 (GND)

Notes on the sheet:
Simple Z80, redrawn from the z80.info test schematic. Symbols are stock KiCad 10.0.7.
U3 is a 27C256, not the drawing's 27C512. Pin 1 is VPP, tied to +5V. A15 only feeds the decoder.
U1 is the Z84C00 symbol (CMOS Z80). U2 is HM62256, value 62256.
No 74HCT14 or 74HCT32 in this library. U7 is a 74HC14 symbol, U8 is a 74LS32 symbol, values set to the HCT parts.
PIO answers any I/O cycle with A7 low (use 00-03). UART answers any with A7 high (use 80-87).
8255 RESET and 16550 MR are active high, after one inverter. Z80 /RESET is after the second.
C2-C11: 100nF, one per IC, drawn here rather than beside each chip.

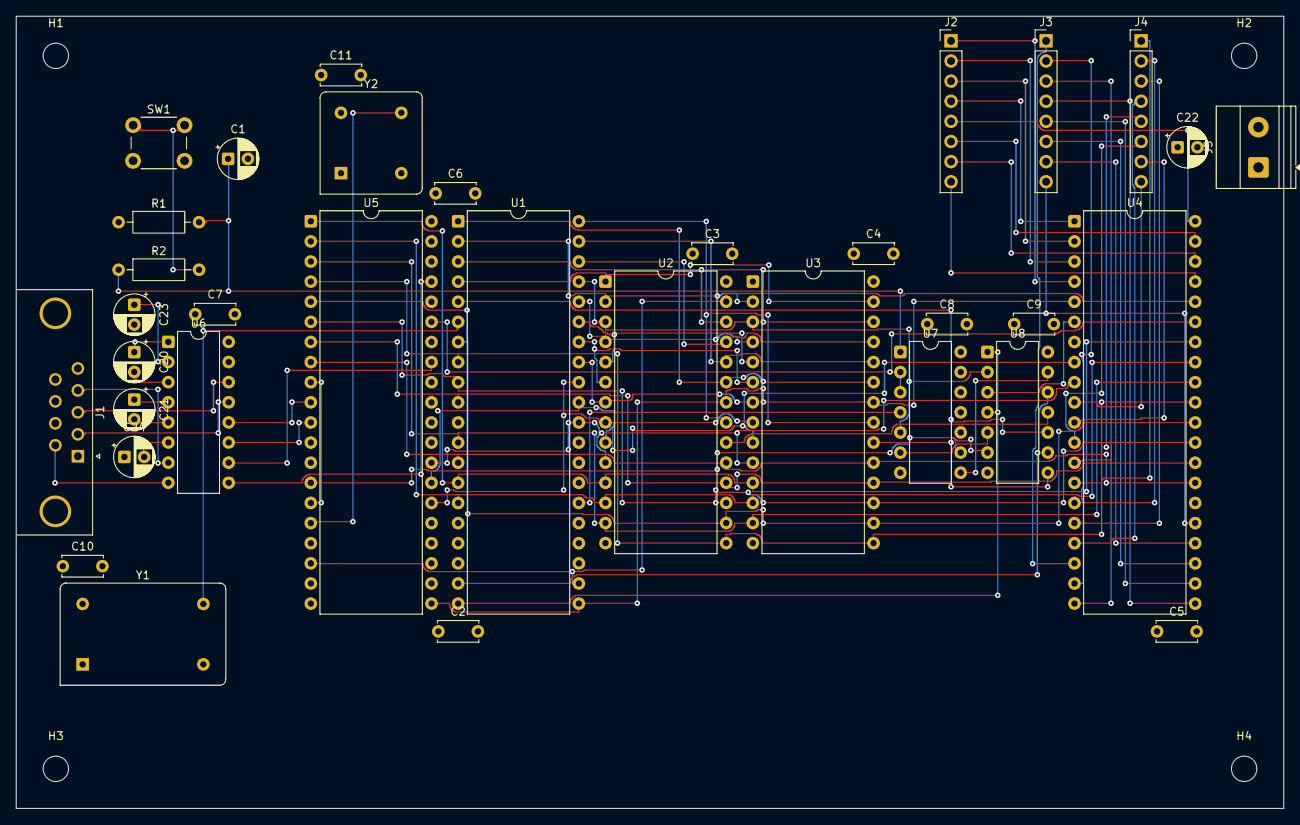
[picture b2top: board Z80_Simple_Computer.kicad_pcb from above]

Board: 4 copper layers, 160.0 x 100.0 mm, 38 parts (0 on the bottom side), 81 nets.
